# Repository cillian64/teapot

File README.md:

# TEApot
TEApot: Tiny Environment Analyser.  A
[ukhasnet](https://www.ukhas.net) node with various sensors.
ukhasnet node IDs `TEA0` through `TEAe`.

# Structure
* [board](board/) contains schematics and board layouts for KiCAD EDA 4
* [case](case/) contains plans for laser-cut cases for the nodes
* [firmware](firmware/) contains firmware for the various node flavours
* [software](software/) contains Python3 software for the USB gateway and
  GridEye receiver.

# Nodes
## Hardware
* Microcontroller: STM32F0 and STM32L0
* Power: AA or D alkaline cell with TLV61225 boost switcher
* Assorted sensors:
    * T: Temperature (HTU21d)
    * H: Humidity (HTU21d)
    * P: Pressure (MS5637)
    * S: Light (TEPT4400)
    * X: 8x8 thermopile array (AMG88 Grid-eye)

## Variants
* r2 was the first set manufactured.  Issues with I2C meant sensors did not
  work.  L0 variants are lower power than F0 but do not support USB.  L0
  variants include a RTC crystal.
* r3 was the second set manufactured, omitting USB but including support
  for the Grid-eye sensor and fixing I2C issues.  All boards include an RTC
  crystal.

Node | Board | Sensors | Status
---- | ----- | ------- | ------
TEA0 | r2 F0 |         | USB Gateway, working
TEA1 | r2 L0 |         | Repeater (needs firmware)
TEA2 | r2 L0 |         | Repeater (needs firmware)
TEA3 | r2 L0 |         | Repeater (needs antenna and firmware)
TEA4 | r2 L0 |         | Repeater (needs antenna and firmware)
TEA5 | r3    | THPS    | Working
TEA6 | r3    | THPS    | Working
TEA7 | r3    | THPS    | Working
TEA8 | r3    | THPS    | Working
TEA9 | r3    | THPS    | Working
TEAa | r3    | THPSX   | Grid-eye has checkerboard problem, otherwise ok
TEAb | r3    | THPSX   | Working
TEAc | r3    | THPSX   | Working
TEAd | r3    | THPSX   | Working
TEAe | r3    | THPSX   | Working

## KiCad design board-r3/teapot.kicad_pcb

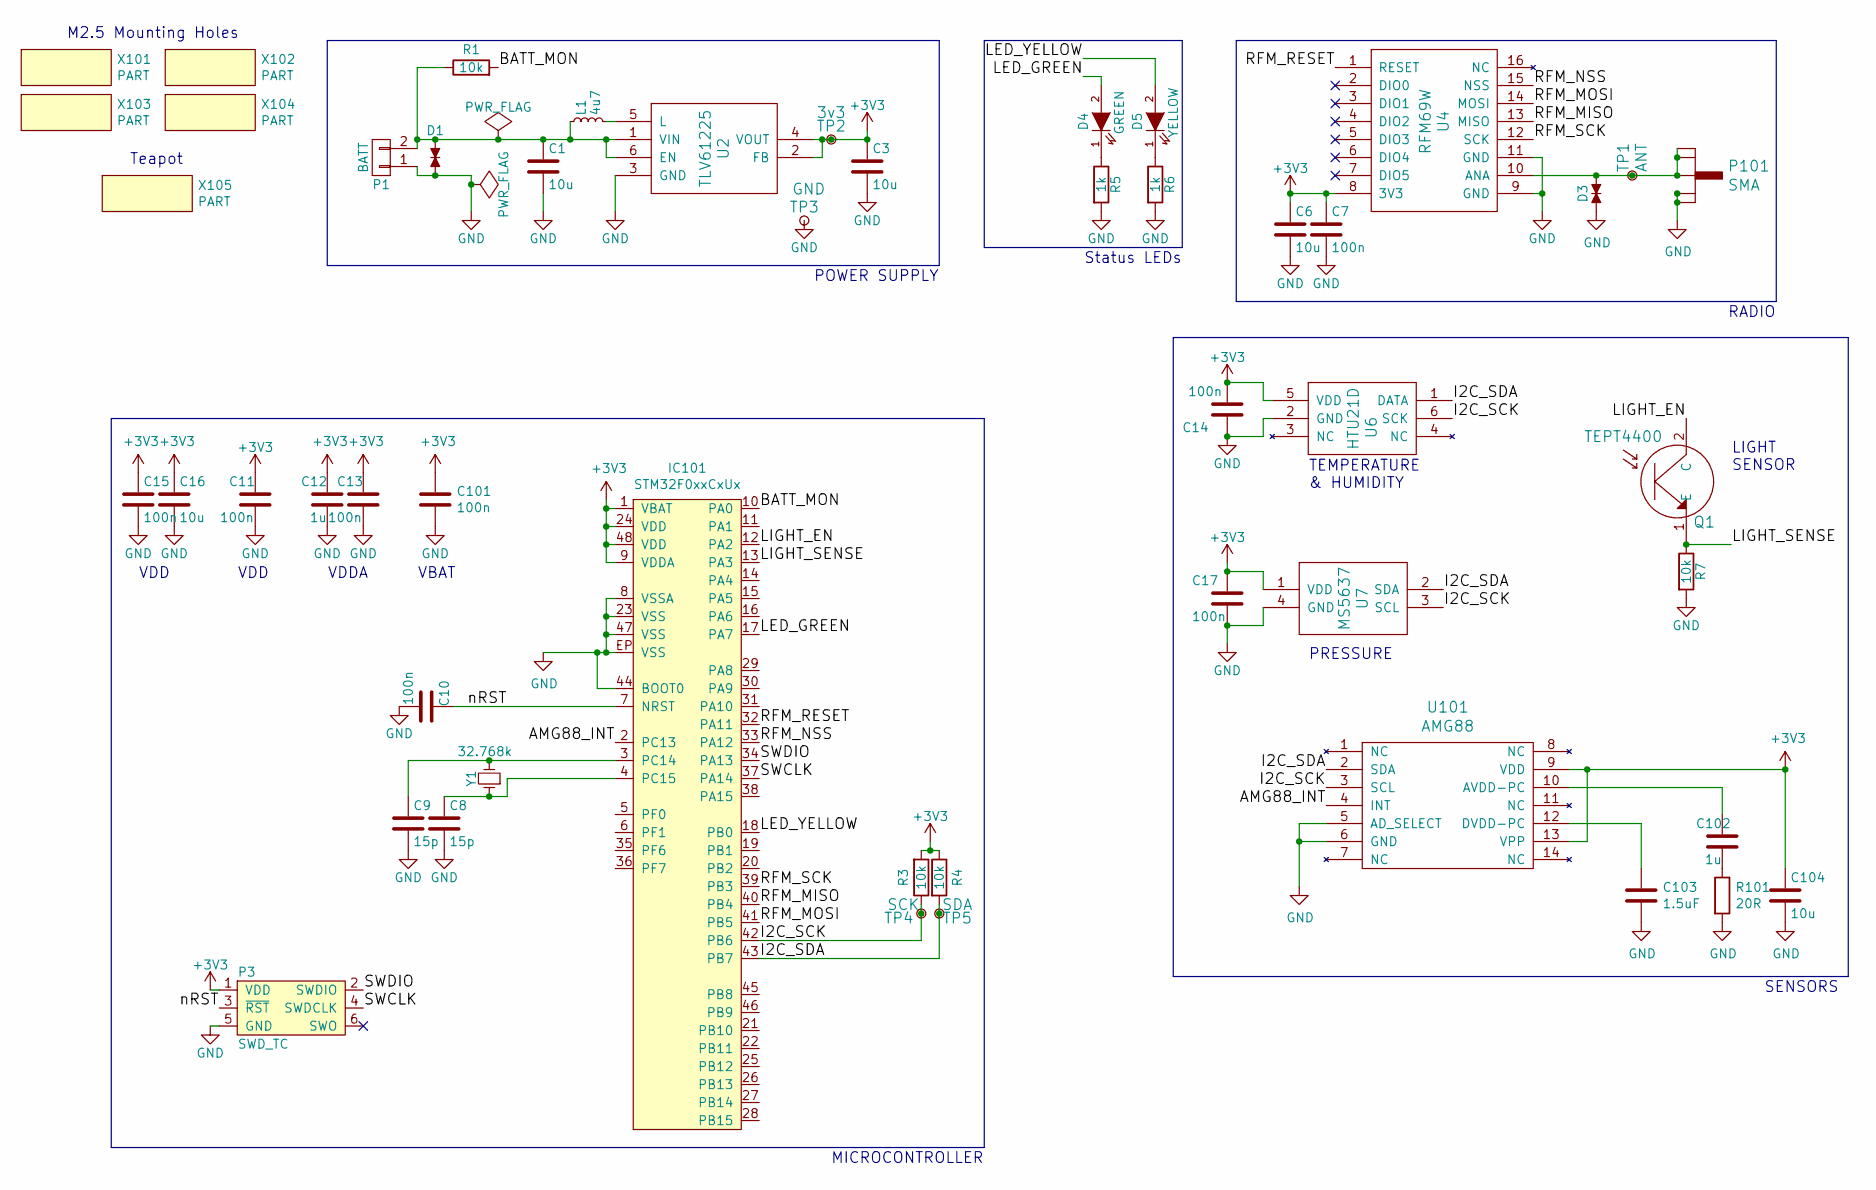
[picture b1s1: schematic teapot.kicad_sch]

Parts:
C1, C3, C6, C16, C104: 10u; C_0603; Farnell 2494230
C7, C10, C11, C13, C14, C15, C17, C101: 100n; C_0603; Farnell 432210
C8, C9: 15p; C_0603; Farnell 1759055
C12, C102: 1u; C_0603; Farnell 2496916
C103: 1.5uF; C_0603; Farnell 2211176
D1, D3: TVS_small; R_0603; Farnell 2368174
D4: GREEN; LED_0805; Farnell 2290331
D5: YELLOW; LED_0805; Farnell 2099242
IC101: STM32F0xxCxUx; QFN-48-EP-ST; Farnell 2469557
L1: 4u7; Inductor_1212; Farnell 2470318
P1: BATT; AA_holder; Farnell 1702629
P3: SWD_TC; TC2030-NL
P101: SMA; SMA-142-0701-801
Q1: TEPT4400; LED-3MM; Farnell SC12389
R1, R3, R4, R7: 10k; R_0603; Farnell 2447230
R5, R6: 1k; R_0603; Farnell 9233385
R101: 20R; R_0603; Farnell 9330798
TP1: ANT; Test_point
TP2: 3v3; Test_point
TP3: GND; Test_point
TP4: SCK; Test_point_mini
TP5: SDA; Test_point_mini
U2: TLV61225; SC-70; Farnell 2492362
U4: RFM69W; RFM69; Farnell RF00489
U6: HTU21D; Farnell 2393536
U7: MS5637; MS563702; Farnell 2362663
U101: AMG88; Farnell 2481446
X101, X102, X103, X104: PART; MountingHole_2.7mm_M2.5
X105: PART; teapot
Y1: 32.768k; XTAL_1206; Farnell 2101347

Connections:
+3V3: C3.1, C6.1, C7.1, C11.1, C12.1, C13.1, C14.2, C15.1, C16.1, C17.1, C101.1, C104.1, IC101.1 (VBAT), IC101.9 (VDDA), IC101.24 (VDD), IC101.48 (VDD), P3.1 (VDD), R3.2, R4.1, TP2.1, U2.2 (FB), U2.4 (VOUT), U4.8 (3V3), U6.5 (VDD), U7.1 (VDD), U101.9 (VDD), U101.13 (VPP)
/AMG88_INT: IC101.2 (PC13), U101.4 (INT)
/BATT_MON: IC101.10 (PA0), R1.2
/I2C_SCK: IC101.42 (PB6), R3.1, TP4.1, U6.6 (SCK), U7.3 (SCL), U101.3 (SCL)
/I2C_SDA: IC101.43 (PB7), R4.2, TP5.1, U6.1 (DATA), U7.2 (SDA), U101.2 (SDA)
/LED_GREEN: D4.2 (A), IC101.17 (PA7)
/LED_YELLOW: D5.2 (A), IC101.18 (PB0)
/LIGHT_EN: IC101.12 (PA2), Q1.2 (C)
/LIGHT_SENSE: IC101.13 (PA3), Q1.1 (E), R7.1
/RFM_MISO: IC101.40 (PB4), U4.13 (MISO)
/RFM_MOSI: IC101.41 (PB5), U4.14 (MOSI)
/RFM_NSS: IC101.33 (PA12), U4.15 (NSS)
/RFM_RESET: IC101.32 (PA11), U4.1 (RESET)
/RFM_SCK: IC101.39 (PB3), U4.12 (SCK)
/SWCLK: IC101.37 (PA14), P3.4 (SWDCLK)
/SWDIO: IC101.34 (PA13), P3.2 (SWDIO)
/nRST: C10.1, IC101.7 (NRST), P3.3 (~RST)
unnamed: C1.1, D1.1, L1.1, P1.2, R1.1, U2.1 (VIN), U2.6 (EN)
unnamed: C8.1, IC101.4 (PC15), Y1.1
unnamed: C9.1, IC101.3 (PC14), Y1.2
unnamed: C102.1, U101.10 (AVDD-PC)
unnamed: C102.2, R101.1
unnamed: C103.1, U101.12 (DVDD-PC)
unnamed: D4.1 (K), R5.1
unnamed: D5.1 (K), R6.1
unnamed: L1.2, U2.5 (L)

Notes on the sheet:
POWER SUPPLY
VBAT
SENSORS
PRESSURE
MICROCONTROLLER
M2.5 Mounting Holes
VDD
Teapot
LIGHT SENSOR
Status LEDs
TEMPERATURE & HUMIDITY
VDDA
RADIO

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
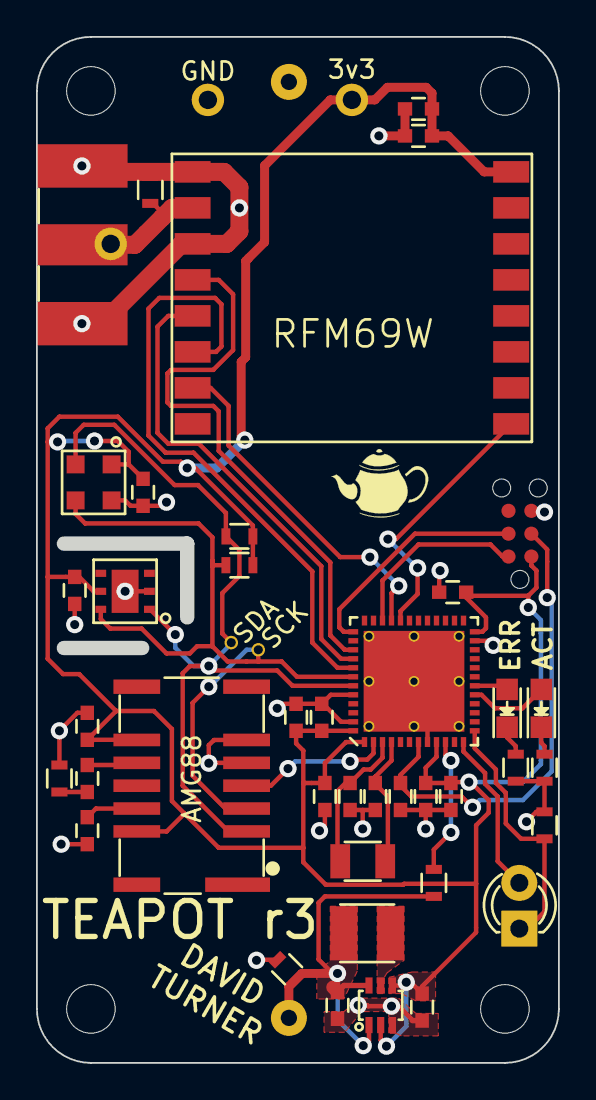
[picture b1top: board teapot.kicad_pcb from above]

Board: 2 copper layers, 28.3 x 56.3 mm, 51 parts (0 on the bottom side), 28 nets.

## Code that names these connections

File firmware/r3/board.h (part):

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/*
 * GPIOA setup:
 *
 * PA0  - BATT_MON                  (analog input).
 * PA1  - PIN1                      (input pullup).
 * PA2  - LIGHT_EN                  (output pushpull).
 * PA3  - LIGHT_SENSE               (analog input).
 * PA4  - PIN4                      (input pullup).
 * PA5  - PIN5                      (input pullup).
 * PA6  - PIN6                      (input pullup).
 * PA7  - LED_GREEN                 (output pushpull).
 * PA8  - PIN8                      (input pullup).
 * PA9  - PIN9                      (input pullup).
 * PA10 - PIN10                     (input pullup).
 * PA11 - RFM_RESET                 (output pushpull).
 * PA12 - RFM_NSS                   (output pushpull).
 * PA13 - SWDAT                     (alternate 0).
 * PA14 - SWCLK                     (alternate 0).
 * PA15 - PIN15                     (input pullup).
 */
#define VAL_GPIOA_MODER             (PIN_MODE_ANALOG(GPIOA_BATT_MON) |         \
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/*
 * GPIOB setup:
 *
 * PB0  - LED_YELLOW                (output pushpull).
 * PB1  - PIN1                      (input pullup).
 * PB2  - PIN2                      (input pullup).
 * PB3  - RFM_SCK                   (alternate 0).
 * PB4  - RFM_MISO                  (alternate 0).
 * PB5  - RFM_MOSI                  (alternate 0).
 * PB6  - I2C_SCK                   (alternate 1).
 * PB7  - I2C_SDA                   (alternate 1).
 * PB8  - PIN8                      (input pullup).
 * PB9  - PIN9                      (input pullup).
 * PB10 - PIN10                     (input pullup).
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 * PC10 - PIN10                     (input pullup).
 * PC11 - PIN11                     (input pullup).
 * PC12 - PIN12                     (input pullup).
 * PC13 - AMG88_INT                 (input pullup).
 * PC14 - OSC32_IN                  (input floating).
 * PC15 - OSC32_OUT                 (input floating).
 */
#define VAL_GPIOC_MODER             (PIN_MODE_INPUT(GPIOC_PIN0) |           \
                                     PIN_MODE_INPUT(GPIOC_PIN1) |           \
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
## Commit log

2015-12-15 thoughts on parts
2015-12-15 renamed to teapot
2015-12-15 Added node IDs
2015-12-15 Schematic: psu, light, pressure, RH
2015-12-15 schematic part for STM32F070F6P6
2015-12-15 Added RFM95W, uC support stuff
2015-12-15 Initial uC pin assignment
2015-12-20 Changed stm32f070 to stm32l052k8u6
    Also did mcu decouplers properly
2015-12-20 Added watch crystal
2015-12-20 Added microusb-b connection
2015-12-20 footprinting
2015-12-20 Fixed derpy footprints
2015-12-20 Footprints and first test board layouts.
2015-12-21 Added USB LDO. Resolves #9
2015-12-21 Added microusb footprint, resolves #6
2015-12-21 Added ESD-protection TVSs. Resolves #7
2015-12-21 Finished speccings parts and footprints.
    Resolves #3
2015-12-21 Fixed a couple of footprint derps
2015-12-22 Power consumption calculations
    Resolves #5, resolves #2
2015-12-22 Added battery level monitor
2015-12-24 added mounting holes. resolves #8
2015-12-27 Initial placement and first successful route.
2015-12-31 gerber export of first test route
2015-12-31 Made schematic look beautiful. Fixes #4
2015-12-31 Setup boardhouse capabilities, track/via spec
2015-12-31 Fixed some ERC issues
2015-12-31 Changed to agg's microusb-ab connector
2015-12-31 New test placement with smaller pcb outline
2015-12-31 Added test points and ANT PTH footprint
2016-01-01 Changed all 0805 (except LEDs) to 0603
2016-01-01 0603 test placement
2016-01-01 layout switcher psu
2016-01-01 Gave UFQFPN apertures and vias
2016-01-01 Routed 3v3 and some GND.
2016-01-02 Added tag-connect for programming
2016-01-02 Second test route on new outline/placement
2016-01-03 Rerouted most of test route 2
2016-01-03 Re-orientated RFM69W
2016-01-03 Updated microusb part
2016-01-05 Moved mounting holes. Fixes #10
2016-01-05 Moved antenna a bit, worked on silk
2016-01-06 Fixed DRC clearance bugs
2016-01-06 Added DIO0,4. Fixes #12
2016-01-06 Final tidying, fixes #11
2016-01-06 Changed mounting to holes, updated gerbers
2016-01-06 Moved LEDs, reduced mask clearance
2016-01-06 Fixed input voltage silk
2016-01-07 Proper mounting holes, fixes #14
2016-01-07 Silk issues, sensor overlap. Fixes #17, #16, #15
2016-01-07 Final fiddling
2016-01-12 Changed to stm32l052k6t6 (lqfp32)
2016-01-12 Added LQFP32, most of first route of new layout
2016-01-12 First layout and route of new lqfp micro
2016-01-25 Added DIO0/4 to schematic
2016-01-25 Routed DIO0+DIO4
2016-01-25 Various fiddling, ready to ship r1 gerbers
2016-02-11 Fixed up capabilities for ragworm, successful manufacture
2016-02-18 r2 BOM
2016-02-18 First test print of case
2016-02-19 Enlarged LED holes to 1.5mm. Resolves #19
    Up from 1mm
2016-02-19 Reduced wall thicknesses to 1mm. Fixes #18
2016-02-19 Lid CSK + reinforcement, fixes #21
2016-02-19 Fixed weird upper ledge, fixes #20
2016-02-19 Updated STLs
2016-02-19 Reduced top and bottom thickness. Fixes #22
2016-02-19 Regenerated STLs
2016-02-23 Initial firmware, i.e. flash LEDs.
2016-02-23 markdown formatting
2016-02-23 use multiline codeblocks
2016-02-23 apparently codeblocks need line spaces
2016-02-23 and we're back to square one
2016-02-24 power spreadsheet time averages
2016-02-24 Most pin assignments and modes
2016-03-18 Updated agg-kicad for stickerbom
2016-03-18 rfm69 skeletons
2016-03-19 Changed libopencm3 to track cillian64 fork
2016-03-19 Filled out RFM69 transmission and basics
2016-03-19 Added reset to rfm69 bringup
2016-03-19 Added some more RFM69 registers we'll need
2016-03-19 Write packet length to FIFO for tx
2016-03-19 Actually release RFM69 from reset
2016-03-19 fix bug in setfreq
2016-03-19 new rfm69 configuration functions
2016-03-19 Rewrote tx function to work with rfm69 strategy
2016-03-19 Transmitter demo (broken)
2016-03-20 Semihosting debug register dump support
2016-03-20 Fix shift direction bug
2016-03-20 Separated bulkwrite w/ & w/ len
2016-03-20 Version check, tx thresh
2016-03-20 Use PA1+PA2
2016-03-20 ukhasnet packet generator and demo
2016-03-20 ADC and light sensor
2016-04-10 Fixed ADC (can only do 12-bit convert)
2016-04-11 Wrote i2c driver. Hopefully.
2016-04-12 Removed 10-bit addressing from i2c driver
2016-04-12 untested ms5637 driver
2016-04-13 Basic htu21d reading
2016-04-13 Removed 10-bit flag from temp/hum i2c reads
2016-04-14 Open drain i2c outputs
2016-04-15 Enable HSI16 oscillator
2016-04-15 Added optional i2c restarting
2016-04-15 debugging htu21d i2c
2016-06-17 Budged agg-kicad to cillian64 fork
2016-06-17 Sch: removed usb, pwr led, swd
2016-06-17 Migated PSU and boilerplate to new QFN-64 micro
2016-06-17 Ripped up old PCB.
2016-06-17 Fixed HTU21D and MS5637 footprints.
    Fixes #37
    Fixes #35
2016-06-17 new board outline with 4xM2.5 mounting holes
2016-06-17 Removed unused part libraries
2016-06-17 Added AMG88 part/fp
2016-06-17 Initial placement
2016-06-17 Second placement
2016-06-17 Pin assignment and final placement??
2016-06-17 First route
2016-06-17 Reinstated SMA, silk fiddling
2016-06-17 Neatened schematic
2016-06-17 Moved ANT TP outside of AA cell holder
2016-06-19 Fixed HTU21D and MS5637 FPs
    Had updated FP files but not updated in board
2016-06-19 Fixed clearance violation, removed bogus silk
2016-06-19 added p1 indicator to AMG88
2016-06-19 Thickened up radio VCC tracks
2016-06-19 Updated gerbs
2016-06-26 Added BOM, spreadsheet and stickerbom
2016-06-27 Updated BOM for old r2 parts found
2016-06-27 Moved old firmware into r2 directory, added readme
2016-06-27 Added ChibiOS checkout
2016-06-28 Updated README for actual STM32 part names
2016-06-28 r2_5 and r3 chibios basics
2016-06-28 r2_5 and r3 board.h files
2016-06-28 Fixed bugs in ChibiOS base setup
2016-06-29 Added flash/debug commands to makefiles
2016-06-29 Analog test driver: doesn't work
2016-06-29 Remove mistakenly added vim swapfile
2016-06-30 Ported basic rfm69 driver to chibios
2016-06-30 Test radio firmware for r2_5 and r3
2016-07-01 Grid-eye demo
2016-07-01 Semihosted demo
2016-07-01 added missing lib
2016-07-01 Made semihosting an optional define in makefile
2016-07-01 Ported HTU21D,MS5637 drivers, though not quite working.
2016-07-04 Disable analog thread
2016-07-04 Disable gcc optimisations: -O0
2016-07-04 Added LED blink on tx
2016-07-04 Stripped down main, changed heartbeat
2016-07-04 USB CDC proof of concept
2016-07-06 Add syncronous receive function for rfm69
2016-07-06 packet buffer should be uint8_t not char
2016-07-06 Add missing include
2016-07-06 ukhasnet_addhop
2016-07-06 Converted all DOS CRLF files to UNIX LF
2016-07-06 Added gateway and repeater logic to r2_5
2016-07-07 Fixed typos, added flash on rx
2016-07-07 Added transmit and sequence logic to r3
2016-07-07 Disable semihosting, disable i2c DMA (clashed with spi)
2016-07-07 Disable heartbeat, clear LEDs on startup
2016-07-07 Set RX bandwidth
2016-07-07 Get packet len from first byte, not register
2016-07-07 Added simple gateway uploader
2016-07-07 Attempted big packets. It didn't work very well
2016-07-07 Wireless grid-eye demonstrator
2016-07-08 Disable interplation in grid-receiver
2017-03-13 new lasercut r3 case
2017-03-14 added node database
2017-03-14 Cleaned up gateway code
2017-03-14 Updated nodelist after bringup
2017-03-14 MBA programmer path
2017-03-15 README
2017-03-15 re-imported board-r2
2017-03-16 Merging grid-eye and sensor r3 software
2017-03-18 grid-eye compress, encode, pack
2017-03-18 Fixed deviation, was twice too wide
2017-03-18 Only 1 hop, and tx less often
2017-03-18 Working grid-eye compression
2017-03-18 Fixed python shebang on osx
2017-03-18 New grid receiver
2017-03-18 grid-eye receiver from ukhn feed
2017-03-19 Panic with reason, fix temp sensor
2017-03-19 Add temperature MSB MSbit bodge
2017-03-19 Added TEApot logtail script
2017-03-19 Made r3 pressure sensor work
2017-03-19 Made analog work on r3
2017-03-19 Sleep mode between senses: 4mA average consumption
2017-03-19 Read/write config to/from flash
2017-03-19 flash config for grideye nodes
2017-03-19 Add grid-eye delay to dodge repeaters
2017-03-19 fix humidity measurement bug
2017-03-19 New low power standby mode
2017-03-19 Set out-of-range humidities to 0 instead of paniccing
2017-03-20 Node status
2017-03-20 homepage photo
2017-08-03 fixed submodules .gitmodules
2017-11-24 Update node inventory
2021-01-17 Update USB CDC path for linux (rather than macos)
2022-08-21 Basic rust gateway to ukhas.net
2022-08-25 Prototype influxdb backend
    Post lines straight to local InfluxDB instead of to the ukhas.net
    gateway
2022-08-25 Update serialport dependency
    The old version of serialport had two issues in its dependencies, so
    update it to the latest.
2022-08-26 Convert r3 PCB to KiCAD v6 format

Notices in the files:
firmware/r3/board.h:
ChibiOS - Copyright (C) 2006..2016 Giovanni Di Sirio
Licensed under the Apache License, Version 2.0 (the "License");
